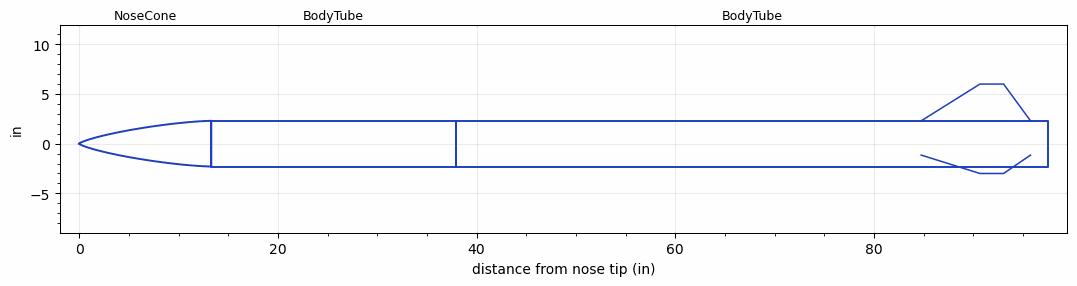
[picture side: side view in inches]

<RASAeroDocument>
 <FileVersion>2</FileVersion>
 <RocketDesign>
  <NoseCone>
   <Length>13.3</Length>
   <Diameter>4.6</Diameter>
   <Shape>Von Karman Ogive</Shape>
   <Location>0</Location>
  </NoseCone>
  <BodyTube>
   <Length>24.6</Length>
   <Diameter>4.6</Diameter>
   <Location>13.3</Location>
  </BodyTube>
  <BodyTube>
   <Length>59.6</Length>
   <Diameter>4.6</Diameter>
   <RailGuideDiameter>0.5</RailGuideDiameter>
   <RailGuideHeight>0.5</RailGuideHeight>
   <Location>37.9</Location>
   <Fin>
    <Count>3</Count>
    <Chord>11</Chord>
    <Span>3.7</Span>
    <SweepDistance>5.91</SweepDistance>
    <TipChord>2.38</TipChord>
    <Thickness>0.3</Thickness>
    <Location>12.75</Location>
    <AirfoilSection>Subsonic NACA</AirfoilSection>
   </Fin>
  </BodyTube>
  <Surface>Smooth (Zero Roughness)</Surface>
  <ModifiedBarrowman>False</ModifiedBarrowman>
  <Turbulence>False</Turbulence>
  <UseBooster1>False</UseBooster1>
  <UseBooster2>False</UseBooster2>
 </RocketDesign>
 <LaunchSite>
  <Altitude>4593</Altitude>
  <Pressure>0</Pressure>
  <RodAngle>6</RodAngle>
  <RodLength>15</RodLength>
  <Temperature>100</Temperature>
  <WindSpeed>0</WindSpeed>
 </LaunchSite>
 <Recovery>
  <Altitude1>1000</Altitude1>
  <Altitude2>1000</Altitude2>
  <DeviceType1>None</DeviceType1>
  <DeviceType2>None</DeviceType2>
  <Event1>False</Event1>
  <Event2>False</Event2>
  <Size1>1</Size1>
  <Size2>1</Size2>
  <EventType1>None</EventType1>
  <EventType2>None</EventType2>
  <CD1>1.33</CD1>
  <CD2>1.33</CD2>
 </Recovery>
 <SimulationList>
  <Simulation>
   <SustainerEngine>M1550R  (AT)</SustainerEngine>
   <SustainerLaunchWt>36.2</SustainerLaunchWt>
   <SustainerNozzleDiameter>1.5</SustainerNozzleDiameter>
   <SustainerCG>55.1</SustainerCG>
   <SustainerIgnitionDelay>0</SustainerIgnitionDelay>
   <Booster1SeparationDelay>0</Booster1SeparationDelay>
   <Booster1IgnitionDelay>0</Booster1IgnitionDelay>
   <IncludeBooster1>False</IncludeBooster1>
   <Booster2Delay>0</Booster2Delay>
   <IncludeBooster2>False</IncludeBooster2>
   <TimetoApogee>27.06052</TimetoApogee>
   <MaxAltitude>12369.14</MaxAltitude>
   <MaxVelocity>1067.326</MaxVelocity>
  </Simulation>
 </SimulationList>
</RASAeroDocument>
